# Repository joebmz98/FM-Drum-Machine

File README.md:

# FM-Drum-Machine
Teensy based frequency modulation drum machine. It uses the Audio Design tool to synthesize drum sounds and has a 16 step sequencer powered by an Arduino Nano.

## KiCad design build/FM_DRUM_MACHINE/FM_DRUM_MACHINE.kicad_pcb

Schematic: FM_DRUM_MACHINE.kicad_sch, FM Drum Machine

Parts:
A1, A2: GY-PCM5102; PCM5102_DAC_BreakoutBoard
C1, C2: 100uF; CP_Radial_D5.0mm_P2.00mm
C3, C4, C5, C6: 10uF; CP_Radial_D5.0mm_P2.00mm
C27, C43, C44, C45, C46, C47, C48, C49, C50, C51, C52, C53, C54, C55, C56, C57, C58, C59, C60, C61, C62, C63, C64, C75, C77, C79, C80: 10nF; C_Disc_P5.08mm
C69, C70, C71, C72, C73, C82: 10uF; C_Disc_P5.08mm
C74, C76, C78, C81: 1uF; C_Disc_P5.08mm
C83, C84, C85, C86, C87: 10Uf; C_Disc_P5.08mm
D1: 1N4148; D_4148_BigPads
D2: LED_STEP1; LED_D5.0mm
D3, D4: RED LED; LED_D5.0mm
D5, D6, D7, D8, D9, D10, D11, D12, D13, D14, D15, D16, D17, D18, D19, D20, D21, D22, D23, D24, D25, D26, D27, D28, D29, D63, D65, D66: 1N4148; D_DO-35_P7.62mm_Horizontal
D30: LED_STEP2; LED_D5.0mm
D31: LED_STEP3; LED_D5.0mm
D32: LED_STEP4; LED_D5.0mm
D33: LED_STEP5; LED_D5.0mm
D34: LED_STEP6; LED_D5.0mm
D35: LED_STEP7; LED_D5.0mm
D36: LED_STEP8; LED_D5.0mm
D37: LED_STEP9; LED_D5.0mm
D38: LED_STEP10; LED_D5.0mm
D39: LED_STEP11; LED_D5.0mm
D40: LED_STEP12; LED_D5.0mm
D41: LED_STEP13; LED_D5.0mm
D42: LED_STEP14; LED_D5.0mm
D43: LED_STEP15; LED_D5.0mm
D44: LED_STEP16; LED_D5.0mm
D45: LED_KICK; LED_D5.0mm
D46: LED_SNARE; LED_D5.0mm
D47: LED_CHAT; LED_D5.0mm
D48: LED_OHAT; LED_D5.0mm
D49: LED_LOTOM; LED_D5.0mm
D50: LED_HITOM; LED_D5.0mm
D51: LED_PLAY/TEMPO; LED_D5.0mm
D52: LED_RECORD; LED_D5.0mm
D53: LED_EXTCLK; LED_D5.0mm
D54: 1N914BWS; D_4148_BigPads; Part Number 1N914BWS; JLCPCB ID C258181
D57, D58, D59, D60, D61, D62, D67: 1N4148; D_DO-35_SOD27_P5.08mm_Vertical_KathodeUp
J1: PJ-102A; CUI_PJ-102A
J2: KICK_BUFFEREDOUT; Jack_3.5mm_CUI_SJ1-3525N_Horizontal_edit
J3: SNARE_BUFFEREDOUT; Jack_3.5mm_CUI_SJ1-3525N_Horizontal_edit
J4: HATS_BUFFEREDOUT; Jack_3.5mm_CUI_SJ1-3525N_Horizontal_edit
J5: TOMS_BUFFEREDOUT; Jack_3.5mm_CUI_SJ1-3525N_Horizontal_edit
J6: LINE_OUT; Jack_3.5mm_CUI_SJ1-3525N_Horizontal_edit
Nano1: Arduino Nano; Arduino_Nano
R1, R3, R5, R13: 820R; R_Axial_DIN0207_L6.3mm_D2.5mm_P7.62mm_Horizontal
R2, R4, R6, R14, R15, R50: 330R; R_Axial_DIN0207_L6.3mm_D2.5mm_P7.62mm_Horizontal
R7, R8, R9, R10, R92, R93, R94, R95: 220R; R_Axial_DIN0207_L6.3mm_D2.5mm_P7.62mm_Horizontal
R11, R57, R58, R63, R64, R65, R66, R67, R68, R69: 10k; R_Axial_DIN0207_L6.3mm_D2.5mm_P7.62mm_Horizontal
R12, R51: 22k; R_Axial_DIN0207_L6.3mm_D2.5mm_P7.62mm_Horizontal
R38, R39, R40, R41, R44, R45, R46, R54, R61, R70, R71, R75, R77, R78, R80, R81, R83, R84, R85, R86, R87: 100k; R_Axial_DIN0207_L6.3mm_D2.5mm_P7.62mm_Horizontal
R52: 680R; R_Axial_DIN0207_L6.3mm_D2.5mm_P7.62mm_Horizontal
R53, R56, R60, R73: 220k; R_Axial_DIN0207_L6.3mm_D2.5mm_P7.62mm_Horizontal
R55, R62, R88: 33k; R_Axial_DIN0207_L6.3mm_D2.5mm_P7.62mm_Horizontal
R59, R74: 1M; R_Axial_DIN0207_L6.3mm_D2.5mm_P7.62mm_Horizontal
R76, R79: 14k; R_Axial_DIN0207_L6.3mm_D2.5mm_P7.62mm_Horizontal
R82: 2k; R_Axial_DIN0207_L6.3mm_D2.5mm_P7.62mm_Horizontal
R89: 4k7; R_Axial_DIN0207_L6.3mm_D2.5mm_P7.62mm_Horizontal
R91: 100R; R_Axial_DIN0207_L6.3mm_D2.5mm_P7.62mm_Horizontal
RV1: KICK_DECAY; Potentiometer_RV09_BigPads
RV2: SWING; Potentiometer_RV09_BigPads
RV3: KICK_TUNE; Potentiometer_RV09_BigPads
RV4: KICK_PUNCH; Potentiometer_RV09_BigPads
RV5: KICK_ATTACK; Potentiometer_RV09_BigPads
RV6: SNARE_DECAY; Potentiometer_RV09_BigPads
RV7, RV9: SNARE_SNAP; Potentiometer_RV09_BigPads
RV8: SNARE_PITCH; Potentiometer_RV09_BigPads
RV10: SNARE_TONE; Potentiometer_RV09_BigPads
RV11: HAT_DECAY; Potentiometer_RV09_BigPads
RV12: HAT_TIMBRE; Potentiometer_RV09_BigPads
RV13: HAT_TONE; Potentiometer_RV09_BigPads
RV14: HAT_RESONANCE; Potentiometer_RV09_BigPads
RV15: LOTOM_DECAY; Potentiometer_RV09_BigPads
RV16: LOTOM_PUNCH; Potentiometer_RV09_BigPads
RV17: LOTOM_TUNE; Potentiometer_RV09_BigPads
RV18: LOTOM_ATTACK; Potentiometer_RV09_BigPads
RV19: HITOM_DECAY; Potentiometer_RV09_BigPads
RV20: HITOM_PUNCH; Potentiometer_RV09_BigPads
RV21: HITOM_TUNE; Potentiometer_RV09_BigPads
RV22: HITOM_ATTACK; Potentiometer_RV09_BigPads
RV27, RV28: 100k; Potentiometer_Alps_RK09L_Double_Vertical
RV29, RV32: 100k; Potentiometer_RV09_BigPads
RV30: A100k; Potentiometer_RV09_BigPads
RV31: 10k; Potentiometer_RV09_BigPads
RV33, RV35, RV40, RV46: B100k; Potentiometer_RV09_BigPads
RV37: TEMPO; Potentiometer_RV09_BigPads
RV38: B20k; Potentiometer_RV09_BigPads
RV39: A1k; Potentiometer_RV09_BigPads
SW1: STEP1; SW_Cherry_MX_PCB_1.00u
SW2: STEP2; SW_Cherry_MX_PCB_1.00u
SW3: STEP3; SW_Cherry_MX_PCB_1.00u
SW4: STEP4; SW_Cherry_MX_PCB_1.00u
SW5: STEP5; SW_Cherry_MX_PCB_1.00u
SW6: STEP6; SW_Cherry_MX_PCB_1.00u
SW7: STEP7; SW_Cherry_MX_PCB_1.00u
SW8: STEP8; SW_Cherry_MX_PCB_1.00u
SW9: STEP9; SW_Cherry_MX_PCB_1.00u
SW10: STEP10; SW_Cherry_MX_PCB_1.00u
SW11: STEP11; SW_Cherry_MX_PCB_1.00u
SW12: STEP12; SW_Cherry_MX_PCB_1.00u
SW13: STEP13; SW_Cherry_MX_PCB_1.00u
SW14: STEP14; SW_Cherry_MX_PCB_1.00u
SW15: STEP15; SW_Cherry_MX_PCB_1.00u
SW16: STEP16; SW_Cherry_MX_PCB_1.00u
SW17: KICK_TRIG; SW_Cherry_MX_PCB_1.00u
SW18: SNARE_TRIG; SW_Cherry_MX_PCB_1.00u
SW19: CHAT_TRIG; SW_Cherry_MX_PCB_1.00u
SW20: OHAT_TRIG; SW_Cherry_MX_PCB_1.00u
SW21: LOTOM_TRIG; SW_Cherry_MX_PCB_1.00u
SW22: HITOM_TRIG; SW_Cherry_MX_PCB_1.00u
SW23: PLAY/PAUSE; SW_Cherry_MX_PCB_1.00u
SW24: RECORD; SW_Cherry_MX_PCB_1.00u
SW25: SELECT; SW_Cherry_MX_PCB_1.00u
SW26, SW27: SW_DPDT_x2; Switch_Toggle_DPDT_SubMini
TRIM1, TRIM2, TRIM3: TrimPot_T73YEt_100k; Potentiometer_Bourns_3296W_Vertical_BigPads; Part Number T73YE104KT20
TRS_JACK_1: MIDI IN TYPE A; Jack_3.5mm_CUI_SJ1-3525N_Horizontal_edit
TRS_JACK_2: MIDI THRU TYPE A; Jack_3.5mm_CUI_SJ1-3525N_Horizontal_edit
TRS_JACK_3: MIDI OUT TYPE A; Jack_3.5mm_CUI_SJ1-3525N_Horizontal_edit
Teensy4.0: Teensy4.0; Teensy40
U1: 6N138; DIP-8_W7.62mm_LongPads
U2: TL072; DIP-8_W7.62mm_LongPads; JLCPCB ID C90748
U3, U12: OPA551P; DIP-8_W7.62mm
U4, U10, U11, U13, U14: TL074; DIP-14_W7.62mm_LongPads
U5: MAX7221xNG; DIP-24_W7.62mm
U6, U7: CD74HC4067M; SOIC-24W_7.5x15.4mm_P1.27mm
U8: AMS1117-5.0; SOT-223-3_TabPin2
U9: AMS1117-3.3; SOT-223-3_TabPin2

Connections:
3.3V: A1.6 (VIN), A1.13 (XSMT), A2.6 (VIN), A2.13 (XSMT), C72.2, RV1.3, RV3.3, RV4.3, RV5.3, RV6.3, RV7.3, RV8.3, RV9.3, RV10.3, RV11.3, RV12.3, RV13.3, RV14.3, RV15.3, RV16.3, RV17.3, RV18.3, RV19.3, RV20.3, RV21.3, RV22.3, U9.2 (VO)
5V: C70.2, C71.2, Nano1.30 (VIN), R8.2, R10.2, R11.2, RV2.3, RV37.3, Teensy4.0.33 (VIN), U1.8 (VCC), U5.19 (V+), U6.24 (VCC), U7.24 (VCC), U8.2 (VO), U9.3 (VI)
12V: C1.1, D54.2 (A), J1.2, J1.3, R70.1, R88.1, U2.8 (V+), U3.7 (V+), U4.4 (V+), U10.4 (V+), U11.4 (V+), U12.7 (V+), U13.4 (V+), U14.4 (V+)
A1BCK: A1.2 (BCK), A2.2 (BCK), Teensy4.0.28 (21_A7_RX5_BCLK1)
A1DIN: A1.3 (DIN), A2.3 (DIN), Teensy4.0.9 (7_RX2_OUT1A)
A1LCK: A1.4 (LCK), A2.4 (LCK), Teensy4.0.27 (20_A6_TX5_LRCLK1)
A1SCK: A1.1 (SCK), A2.1 (SCK), Teensy4.0.30 (23_A9_CRX1_MCLK1)
AGND: A1.8 (AGND), A1.10 (AGND), A2.8 (AGND), A2.10 (AGND)
CLK: Nano1.16 (D13), U5.13 (CLK)
COMPRESSOR_OUT: RV32.2, RV32.3, SW26.2 (B), U10.8
CS/LOAD: Nano1.13 (D10), U5.12 (~CS)
DGND: A1.5 (GND), A1.12 (FMT), A1.14 (DEMP), A1.15 (FLT), A2.5 (GND), A2.12 (FMT), A2.14 (DEMP), A2.15 (FLT), C2.2, C27.2, C43.2, C44.2, C45.2, C46.2, C47.2, C48.2, C49.2, C50.2, C51.2, C52.2, C53.2, C54.2, C55.2, C56.2, C57.2, C58.2, C59.2, C60.2, C61.2, C62.2, C63.2, C64.2, C69.1, C70.1, C71.1, C72.1, C73.1, J1.1, J2.S, J3.S, J4.S, J5.S, J6.S, Nano1.4 (GND), Nano1.29 (GND), R65.1, R66.1, R67.1, R68.1, R69.1, R71.2, RV1.1, RV2.1, RV3.1, RV4.1, RV5.1, RV6.1, RV7.1, RV8.1, RV9.1, RV10.1, RV11.1, RV12.1, RV13.1, RV14.1, RV15.1, RV16.1, RV17.1, RV18.1, RV19.1, RV20.1, RV21.1, RV22.1, RV33.1, RV35.1, RV37.1, RV39.1, RV40.1, RV46.1, TRS_JACK_1.S, TRS_JACK_2.S, TRS_JACK_3.S, Teensy4.0.1 (GND), Teensy4.0.32 (GND), U1.5 (GND), U2.4 (V-), U3.4 (V-), U3.8 (Flag), U4.11 (V-), U5.4 (GND), U5.9 (GND), U6.12 (GND), U6.15 (~E), U7.12 (GND), U7.15 (~E), U8.1 (GND), U9.1 (GND), U10.11 (V-), U11.11 (V-), U12.4 (V-), U12.8 (Flag), U13.11 (V-), U14.11 (V-)
DIG0: D2.1 (K), D34.1 (K), D39.1 (K), D44.1 (K), D49.1 (K), U5.2 (DIG_0)
DIG1: D30.1 (K), D35.1 (K), D40.1 (K), D45.1 (K), D50.1 (K), U5.11 (DIG_1)
DIG2: D31.1 (K), D36.1 (K), D41.1 (K), D46.1 (K), D51.1 (K), U5.6 (DIG_2)
DIG3: D32.1 (K), D37.1 (K), D42.1 (K), D47.1 (K), D52.1 (K), U5.7 (DIG_3)
DIG4: D33.1 (K), D38.1 (K), D43.1 (K), D48.1 (K), D53.1 (K), U5.3 (DIG_4)
DIN: Nano1.14 (D11), U5.1 (DIN)
HATSBUFFER_IN: C5.1, R4.2, R40.1, U14.10 (+)
HATS_DCBIAS_IN: C5.2, RV33.3
HATS_OUT: A2.7 (LOUT), RV33.2
HAT_DECAY: C53.1, RV11.2, U6.22 (I9)
HAT_RESONANCE: C56.1, RV14.2, U6.19 (I12)
HAT_TIMBRE: C54.1, RV12.2, U6.20 (I11)
HAT_TONE: C55.1, RV13.2, U6.21 (I10)
HITOM_ATTACK: C64.1, RV22.2, U7.2 (I7)
HITOM_DECAY: C61.1, RV19.2, U7.5 (I4)
HITOM_PITCH: C63.1, RV21.2, U7.4 (I5)
HITOM_PUNCH: C62.1, RV20.2, U7.3 (I6)
HPFSTAGE_OUT: R59.1, SW26.5 (B), SW27.2 (B)
HPF_IN: C74.1, SW26.3 (C)
HPF_OUT: C76.2, R56.1, SW26.6 (C)
KICKBUFFER_IN: C3.1, R38.1, R50.2, U14.3 (+)
KICK_ATTACK: C47.1, RV5.2, U6.6 (I3)
KICK_DCBIAS_IN: C3.2, RV46.3
KICK_DECAY: C44.1, RV1.2, U6.9 (I0)
KICK_OUT: A1.7 (LOUT), RV46.2
KICK_PUNCH: C46.1, RV4.2, U6.7 (I2)
KICK_TUNE: C45.1, RV3.2, U6.8 (I1)
LOTOM_ATTACK: C60.1, RV18.2, U7.6 (I3)
LOTOM_DECAY: C57.1, RV15.2, U7.9 (I0)
LOTOM_PUNCH: C58.1, RV16.2, U7.7 (I2)
LOTOM_TUNE: C59.1, RV17.2, U7.8 (I1)
LPFSTAGE_OUT: R74.1, SW27.5 (B), U13.12 (+)
LPF_IN: C78.1, SW27.3 (C)
LPF_OUT: C81.2, R73.1, SW27.6 (C)
MIDI IN: Nano1.2 (D0/RX), R8.1, U1.6 (VO2)
MIDI OUT: Nano1.1 (D1/TX), R9.2, Teensy4.0.2 (0_RX1_CRX2_CS1)
MIXER_OUT: R46.2, R75.1, U2.1
unnamed: C74.2, R53.1, R54.1
unnamed: C77.1, R57.1, U4.14
unnamed: C78.2, R60.1, R61.1
unnamed: C79.1, R63.1, U11.14
unnamed: C83.2, RV39.2
unnamed: C84.2, R92.2
unnamed: C85.2, R93.2
unnamed: C86.2, R94.2
unnamed: C87.2, R95.2
unnamed: D1.2 (A), TRS_JACK_1.T, TRS_JACK_2.T, U1.3 (C2)
unnamed: D1.1 (K), R7.1, U1.2 (C1)
unnamed: D3.1 (K), D4.2 (A), R51.2, R52.2, U13.13 (-)
unnamed: D5.2 (A), SW1.2
unnamed: D6.2 (A), SW2.2
unnamed: D7.2 (A), SW3.2
unnamed: D8.2 (A), SW4.2
unnamed: D9.2 (A), SW5.2
unnamed: D10.2 (A), SW6.2
unnamed: D11.2 (A), SW7.2
unnamed: D12.2 (A), SW8.2
unnamed: D13.2 (A), SW9.2
unnamed: D14.2 (A), SW10.2
unnamed: D15.2 (A), SW11.2
unnamed: D16.2 (A), SW12.2
unnamed: D17.2 (A), SW13.2
unnamed: D18.2 (A), SW14.2
unnamed: D19.2 (A), SW15.2
unnamed: D20.2 (A), SW16.2
unnamed: D21.2 (A), SW17.2
unnamed: D22.2 (A), SW18.2
unnamed: D23.2 (A), SW19.2
unnamed: D24.2 (A), SW20.2
unnamed: D25.2 (A), SW21.2
unnamed: D26.2 (A), SW22.2
unnamed: D27.2 (A), SW23.2
unnamed: D28.2 (A), SW24.2
unnamed: D29.2 (A), SW25.2
unnamed: C69.2, D54.1 (K), U8.3 (VI)
unnamed: D57.2 (A), D58.1 (K)
unnamed: D57.1 (K), D60.2 (A), R77.2, U10.12 (+)
unnamed: D58.2 (A), D59.1 (K)
unnamed: D59.2 (A), R81.1, R82.2
unnamed: D60.1 (K), D61.2 (A)
unnamed: D61.1 (K), D62.2 (A)
unnamed: D62.1 (K), R80.2, U10.7
unnamed 94: D63.2 (A), D65.1 (K); also elsewhere on the board
unnamed: D63.1 (K), D66.2 (A), R83.2, U13.9 (-)
unnamed: D65.2 (A), D66.1 (K), R82.1, U13.8
unnamed: D67.2 (A), U13.1
unnamed 99: D67.1 (K), TRIM2.3 (Right); also elsewhere on the board
unnamed: J2.T, R92.1
unnamed: J3.T, R93.1
unnamed: J4.T, R94.1
unnamed: J5.T, R95.1
unnamed: J6.T, R91.1
unnamed: R1.2, RV28.1
unnamed: R5.1, RV27.1
unnamed: R7.2, TRS_JACK_1.R, TRS_JACK_2.R
unnamed: R9.1, TRS_JACK_3.T
unnamed: R10.1, TRS_JACK_3.R
unnamed: R14.2, RV29.1
unnamed: R44.2, R45.1, U2.7
unnamed: R52.1, RV38.1, RV38.2
unnamed: R84.2, RV30.1, U13.7
unnamed: R85.1, RV31.2
unnamed: R88.2, RV31.3
unnamed: R91.2, RV39.3
unnamed: SW26.1 (A), SW26.4 (A)
unnamed: SW27.1 (A), SW27.4 (A)
unnamed: TRIM1.2 (Center), U4.12 (+)
unnamed: R15.2, TRIM1.1 (Left)
unnamed: C76.1, TRIM1.3 (Right), U4.8, U4.9 (-)
unnamed 122: C82.2, R86.1, TRIM2.1 (Left), TRIM2.2 (Center), TRIM3.3 (Right), U13.2 (-); also elsewhere on the board
unnamed 123: R89.2, TRIM3.1 (Left), TRIM3.2 (Center); also elsewhere on the board
unnamed: R45.2, R46.1, U2.2 (-)
unnamed: R38.2, R39.2, R40.2, R41.2, R44.1, U2.6 (-)
unnamed: C73.2, R70.2, R71.1, U3.3 (+)
unnamed: R54.2, R55.2, U4.3 (+)
unnamed: C75.1, U4.1, U4.2 (-)
unnamed: C77.2, RV27.2, RV27.3, U4.5 (+)
unnamed: R13.1, R13.2, RV27.4, U4.6 (-), U4.7
unnamed: C75.2, RV27.5, RV27.6, U4.10 (+)
unnamed: R57.2, R58.1, U4.13 (-)
unnamed: R11.1, U5.18 (ISET)
unnamed: R75.2, R76.2, U10.3 (+)
unnamed: R77.1, U10.1, U10.2 (-)
unnamed: R80.1, R81.2, U10.6 (-)
unnamed: R78.2, U10.10 (+), U10.14, U13.3 (+)
unnamed: R12.2, RV32.1, U10.9 (-)
unnamed: R78.1, R79.2, U10.13 (-)
unnamed: R61.2, R62.2, U11.3 (+)
unnamed: R1.1, U11.1, U11.2 (-)
unnamed: C79.2, RV28.2, RV28.3, U11.5 (+)
unnamed: R3.1, R3.2, RV28.4, U11.6 (-), U11.7
unnamed: C80.2, RV28.5, RV28.6, U11.10 (+)
unnamed: C81.1, RV29.3, U11.8, U11.9 (-)
unnamed: RV29.2, U11.12 (+)
unnamed: R63.2, R64.1, U11.13 (-)
unnamed: C1.2, C2.1, U3.2 (-), U3.6, U12.3 (+)
unnamed: R86.2, R87.2, U13.5 (+)
unnamed: R84.1, R85.2, U13.6 (-)
unnamed: RV30.2, U13.10 (+)
unnamed: C84.1, U14.1, U14.2 (-)
unnamed: C85.1, U14.6 (-), U14.7
unnamed: C86.1, U14.8, U14.9 (-)
unnamed: C87.1, U14.13 (-), U14.14
SEGA: D2.2 (A), D30.2 (A), D31.2 (A), D32.2 (A), D33.2 (A), U5.14 (SEG_A)
SEGB: D34.2 (A), D35.2 (A), D36.2 (A), D37.2 (A), D38.2 (A), U5.16 (SEG_B)
SEGC: D39.2 (A), D40.2 (A), D41.2 (A), D42.2 (A), D43.2 (A), U5.20 (SEG_C)
SEGD: D44.2 (A), D45.2 (A), D46.2 (A), D47.2 (A), D48.2 (A), U5.23 (SEG_D)
SEGE: D49.2 (A), D50.2 (A), D51.2 (A), D52.2 (A), D53.2 (A), U5.21 (SEG_E)
SNAREBUFFER_IN: C4.1, R2.2, R39.1, U14.5 (+)
SNARE_DCBIAS_IN: RV40.3
SNARE_DECAY: C48.1, RV6.2, U6.5 (I4)
SNARE_OUT: A1.9 (ROUT), RV40.2
SNARE_PITCH: C50.1, RV8.2, U6.4 (I5)
SNARE_PUNCH: C49.1, RV7.2, U6.3 (I6)
SNARE_SNAP: C51.1, RV9.2, U6.2 (I7)
SNARE_TONE: C52.1, RV10.2, U6.23 (I8)
SOFTCLIP_OUT: C83.1, D3.2 (A), D4.1 (K), R51.1, U13.14
SWING: C43.1, Nano1.25 (A6), RV2.2
TEMPO: C27.1, Nano1.24 (A5), RV37.2
TOMSBUFFER_IN: C6.1, R6.2, R41.1, U14.12 (+)
TOMS_DCBIAS_IN: C6.2, RV35.3
TOMS_OUT: A2.9 (ROUT), RV35.2
U6S0: Teensy4.0.11 (9_OUT1C), U6.10 (S0)
U6S1: Teensy4.0.12 (10_CS_MQSR), U6.11 (S1)
U6S2: Teensy4.0.13 (11_MOSI_CTX1), U6.14 (S2)
U6S3: Teensy4.0.14 (12_MISO_MQSL), U6.13 (S3)
U6SIG: Teensy4.0.21 (14_A0_TX3_SPDIF_OUT), U6.1 (COM)
U7S0: Teensy4.0.23 (16_A2_RX4_SCL1), U7.10 (S0)
U7S1: Teensy4.0.24 (17_A3_TX4_SDA1), U7.11 (S1)
U7S2: Teensy4.0.25 (18_A4_SDA0), U7.14 (S2)
U7S3: Teensy4.0.26 (19_A5_SCL0), U7.13 (S3)
U7SIG: Teensy4.0.22 (15_A1_RX3_SPDIF_IN), U7.1 (COM)
Vref: C80.1, C82.1, R2.1, R4.1, R5.2, R6.1, R12.1, R14.1, R15.1, R50.1, R53.2, R55.1, R56.2, R58.2, R59.2, R60.2, R62.1, R64.2, R73.2, R74.2, R76.1, R79.1, R83.1, R87.1, R89.1, RV30.3, RV31.1, RV38.3, U2.3 (+), U2.5 (+), U10.5 (+), U12.2 (-), U12.6
X0: Nano1.19 (A0), R65.2, SW1.1, SW6.1, SW11.1, SW16.1, SW21.1
X1: Nano1.20 (A1), R66.2, SW2.1, SW7.1, SW12.1, SW17.1, SW22.1
X2: Nano1.21 (A2), R67.2, SW3.1, SW8.1, SW13.1, SW18.1, SW23.1
X3: Nano1.22 (A3), R68.2, SW4.1, SW9.1, SW14.1, SW19.1, SW24.1
X4: Nano1.23 (A4), R69.2, SW5.1, SW10.1, SW15.1, SW20.1, SW25.1
Y0: D5.1 (K), D6.1 (K), D7.1 (K), D8.1 (K), D9.1 (K), Nano1.5 (D2)
Y1: D10.1 (K), D11.1 (K), D12.1 (K), D13.1 (K), D14.1 (K), Nano1.6 (D3)
Y2: D15.1 (K), D16.1 (K), D17.1 (K), D18.1 (K), D19.1 (K), Nano1.7 (D4)
Y3: D20.1 (K), D21.1 (K), D22.1 (K), D23.1 (K), D24.1 (K), Nano1.8 (D5)
Y4: D25.1 (K), D26.1 (K), D27.1 (K), D28.1 (K), D29.1 (K), Nano1.9 (D6)

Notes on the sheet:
MORITZ KLEIN LPF
INPUT POWER
RATIO
FILTER STAGE
LO TOM
GAIN
DIGITAL SECTION
MIDI OUTPUT STAGE
DIFFERENTIAL MIXER
CUT-OFF DUAL POT
LPF W/ RESONANCE
RELEASE
PASSIVE ATTENUATORS
RESONANCE TRIM POT
DRIVE
ANALOGUE SECTION
MAX7219
MIDI INPUT STAGE
SOFT CLIP STAGE
LEVEL POTS
HI TOM
SEQUENCER BUTTON MTRX
FM DRUMS
MASTER OUTPUT STAGE
POWER SECTION
MORITZ KLEIN COMPRESSOR
MORITZ KLEIN HPF
TEENSY
KICK
SEQUENCER_POTS
MIXER STAGE
HPF SEMI-RESONANT
SEQUENCER PROCESSOR
MASTER VOLUME
LEDS
SEQUENCER LED MTRX
DC BIASING
DACS
VIRTUAL RAILS
THRESHOLD

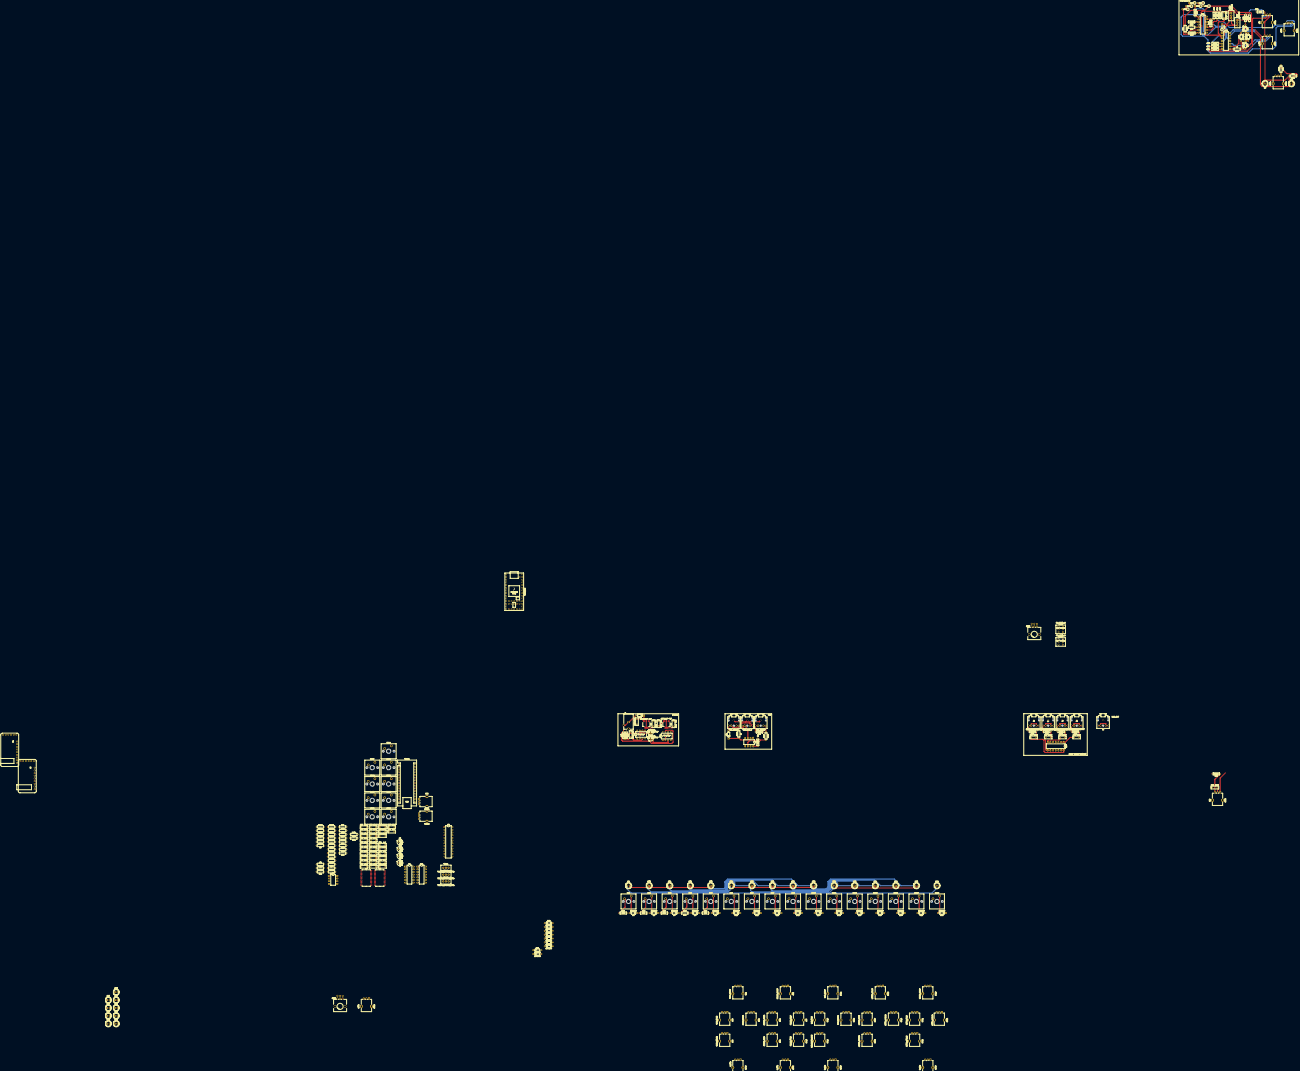
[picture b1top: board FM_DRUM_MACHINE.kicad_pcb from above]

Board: 2 copper layers, 273 parts (0 on the bottom side), 194 nets.

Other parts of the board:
ATTACK: 100k; Potentiometer_Bourns_3296W_Vertical_BigPads
D64: 1N4148; D_DO-35_P7.62mm_Horizontal
RELEASE: 100k; Potentiometer_Bourns_3296W_Vertical_BigPads

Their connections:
unnamed 94: D64.1 (K); also elsewhere on the board
unnamed 99: ATTACK.3 (Right); also elsewhere on the board
unnamed 122: ATTACK.1 (Left), ATTACK.2 (Center), RELEASE.3 (Right); also elsewhere on the board
unnamed 123: RELEASE.1 (Left), RELEASE.2 (Center); also elsewhere on the board

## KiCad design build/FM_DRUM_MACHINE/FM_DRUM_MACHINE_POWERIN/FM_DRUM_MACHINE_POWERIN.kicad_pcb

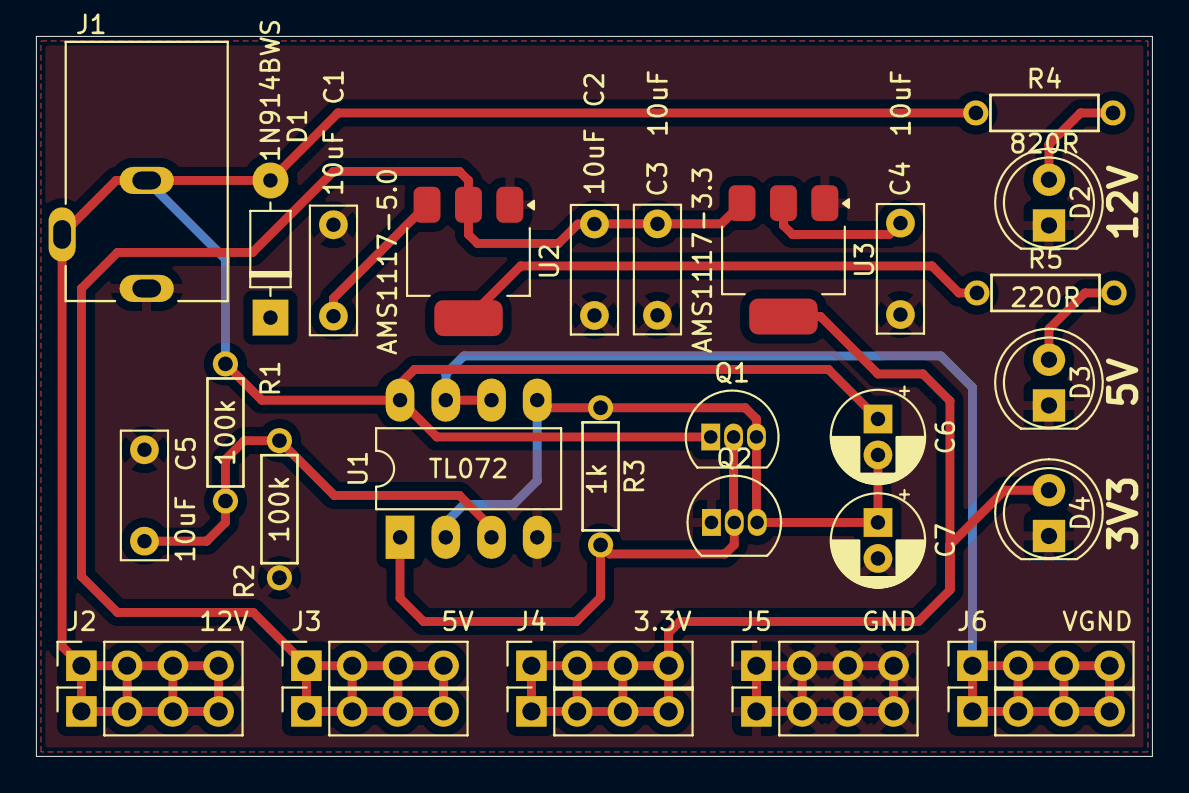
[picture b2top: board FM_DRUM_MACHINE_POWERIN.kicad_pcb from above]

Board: 2 copper layers, 62.0 x 40.0 mm, 32 parts (0 on the bottom side), 11 nets.

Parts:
C1, C2, C3, C4, C5: 10uF; C_Disc_P5.08mm
C6, C7: 100uF; CP_Radial_D5.0mm_P2.00mm
D1: 1N914BWS; D_4148_BigPads
D2, D3, D4: LED; LED_D5.0mm
J1: PJ-102A; CUI_PJ-102A
J2, J2#2: 12V; PinSocket_1x04_P2.54mm_Vertical
J3, J3#2: 5V; PinSocket_1x04_P2.54mm_Vertical
J4, J4#2: 3.3V; PinSocket_1x04_P2.54mm_Vertical
J5, J5#2: GND; PinSocket_1x04_P2.54mm_Vertical
J6, J6#2: VGND; PinSocket_1x04_P2.54mm_Vertical
Q1: BC547; TO-92L_Inline
Q2: BC557; TO-92_Inline
R1, R2: 100k; R_Axial_DIN0207_L6.3mm_D2.5mm_P7.62mm_Horizontal
R3: 1k; R_Axial_DIN0207_L6.3mm_D2.5mm_P7.62mm_Horizontal
R4: 820R; R_Axial_DIN0207_L6.3mm_D2.5mm_P7.62mm_Horizontal
R5: 220R; R_Axial_DIN0207_L6.3mm_D2.5mm_P7.62mm_Horizontal
U1: TL072; DIP-8_W7.62mm_LongPads
U2: AMS1117-5.0; SOT-223-3_TabPin2
U3: AMS1117-3.3; SOT-223-3_TabPin2

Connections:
3.3V: C4.2, D4.2 (A), J4.1, J4.2, J4.3, J4.4, J4#2.1, J4#2.2, J4#2.3, J4#2.4, U3.2 (VO)
5V: C2.2, C3.2, J3.1, J3.2, J3.3, J3.4, J3#2.1, J3#2.2, J3#2.3, J3#2.4, R5.2, U2.2 (VO), U3.3 (VI)
12V: C6.1, D1.2 (A), J1.2, J1.3, J2.1, J2.2, J2.3, J2.4, J2#2.1, J2#2.2, J2#2.3, J2#2.4, Q1.1 (C), R1.1, R4.2, U1.8 (V+)
GND: C1.1, C2.1, C3.1, C4.1, C5.1, C7.2, D2.1 (K), D3.1 (K), D4.1 (K), J1.1, J5.1, J5.2, J5.3, J5.4, J5#2.1, J5#2.2, J5#2.3, J5#2.4, Q2.1 (C), R2.2, U1.4 (V-), U2.1 (GND), U3.1 (GND)
unnamed: C1.2, D1.1 (K), U2.3 (VI)
unnamed: D2.2 (A), R4.1
unnamed: D3.2 (A), R5.1
unnamed: Q1.2 (B), Q2.2 (B), R3.1, U1.1
unnamed: C6.2, C7.1, Q1.3 (E), Q2.3 (E), R3.2, U1.2 (-), U1.5 (+)
unnamed: C5.2, R1.2, R2.1, U1.3 (+)
VGND: J6.1, J6.2, J6.3, J6.4, J6#2.1, J6#2.2, J6#2.3, J6#2.4, U1.6 (-), U1.7

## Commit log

2025-08-20 v0.1.0
    - Initial Schematic Push
2025-08-21 v0.2
    - Further Schematic Modifications
2025-08-21 v0.3
    - Circuit schematic update
2025-08-21 V0.3
2025-08-21 v0.4.0
    - Modified mixer stage. Passive attenuators before DC bias to use the Differential Amplifier as a mixer.
2025-08-21 v0.4
2025-08-21 v0.5
2025-08-22 v0.5
    POWER IN BOARD
2025-08-22 v0.5.1
2025-08-22 v0.5.2
2025-08-22 v0.5.3
2025-08-23 v0.5.5
    - Drive section modified based on testing
    - LPF/HPF Based on testing
2025-08-25 v0.6
2025-08-31 Sound Design Edits
2025-08-31 FM_ENGINE
2025-09-01 Update FM_DRUM_ENGINE
    - Added the new HiHat design. It's monophonic and listens for both hi hat midi notes.
2025-09-01 Schematic Changes
2025-09-01 FM_HATS Prototype Voice
2025-09-01 Hi Hats added to ENGINE
2025-09-02 Prototype Tom Voices
    - Added prototype tom voices
    - Removed pitch envelope control from the kick
2025-09-02 Ground Loop Isolation
    - Filtered +12V to help with noise. This also filters the Vref rail
    - Separated. the DGND from AGND
2025-09-02 Ground Isolation
2025-09-02 Drum Engine Tweaks
2025-09-02 Sequencer adjustments
    - Added Tempo Pot
    - slightly improved step recording
    - Added Swing pot
2025-09-03 PCB Changes
2025-09-03 compressor edits
2025-09-05 LT_SPICE SImulations
2025-09-05 Schematic PCB Changes
    - Updated Power In
    - Updated PCB
